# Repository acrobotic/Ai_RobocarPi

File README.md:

# Ai_RobocarPi

Hardware, Software, and Documentation files for a Raspberry Pi-powered autonomous wheeled robot.

## Description

Developed by MakerBro for ACROBOTIC Industries.  Please consider buying 
products from us to help fund future Open-Source projects like this! We'll
always put our best effort in every project, and release all our design 
files and code for you to use. 

Visit our online shop, which is located at:

   * https://acrobotic.com/

## License

Released under the MIT license. Please check LICENSE.txt for more information. 
All text above must be included in any redistribution.

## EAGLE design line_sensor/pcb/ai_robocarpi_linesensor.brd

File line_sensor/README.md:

## line_sensor 

PCB design files (EAGLE) of an analog optical detector for measuring differences
in light levels. Features 3 QRE1113 reflective sensors and 1 LDR.

## Description

Visit our online shop at:

   * https://acrobotic.com/

Designed by ACROBOTIC Industries.  Please consider buying products from us to 
help fund future Open-Source projects like this! We’ll always put our best 
effort in every project, and release all our design files and code for you to 
use. 

## License

Released under the Creative Commons Attribution, Share-Alike license. Please 
check LICENSE.txt for more information. All text above must be included in any 
redistribution.

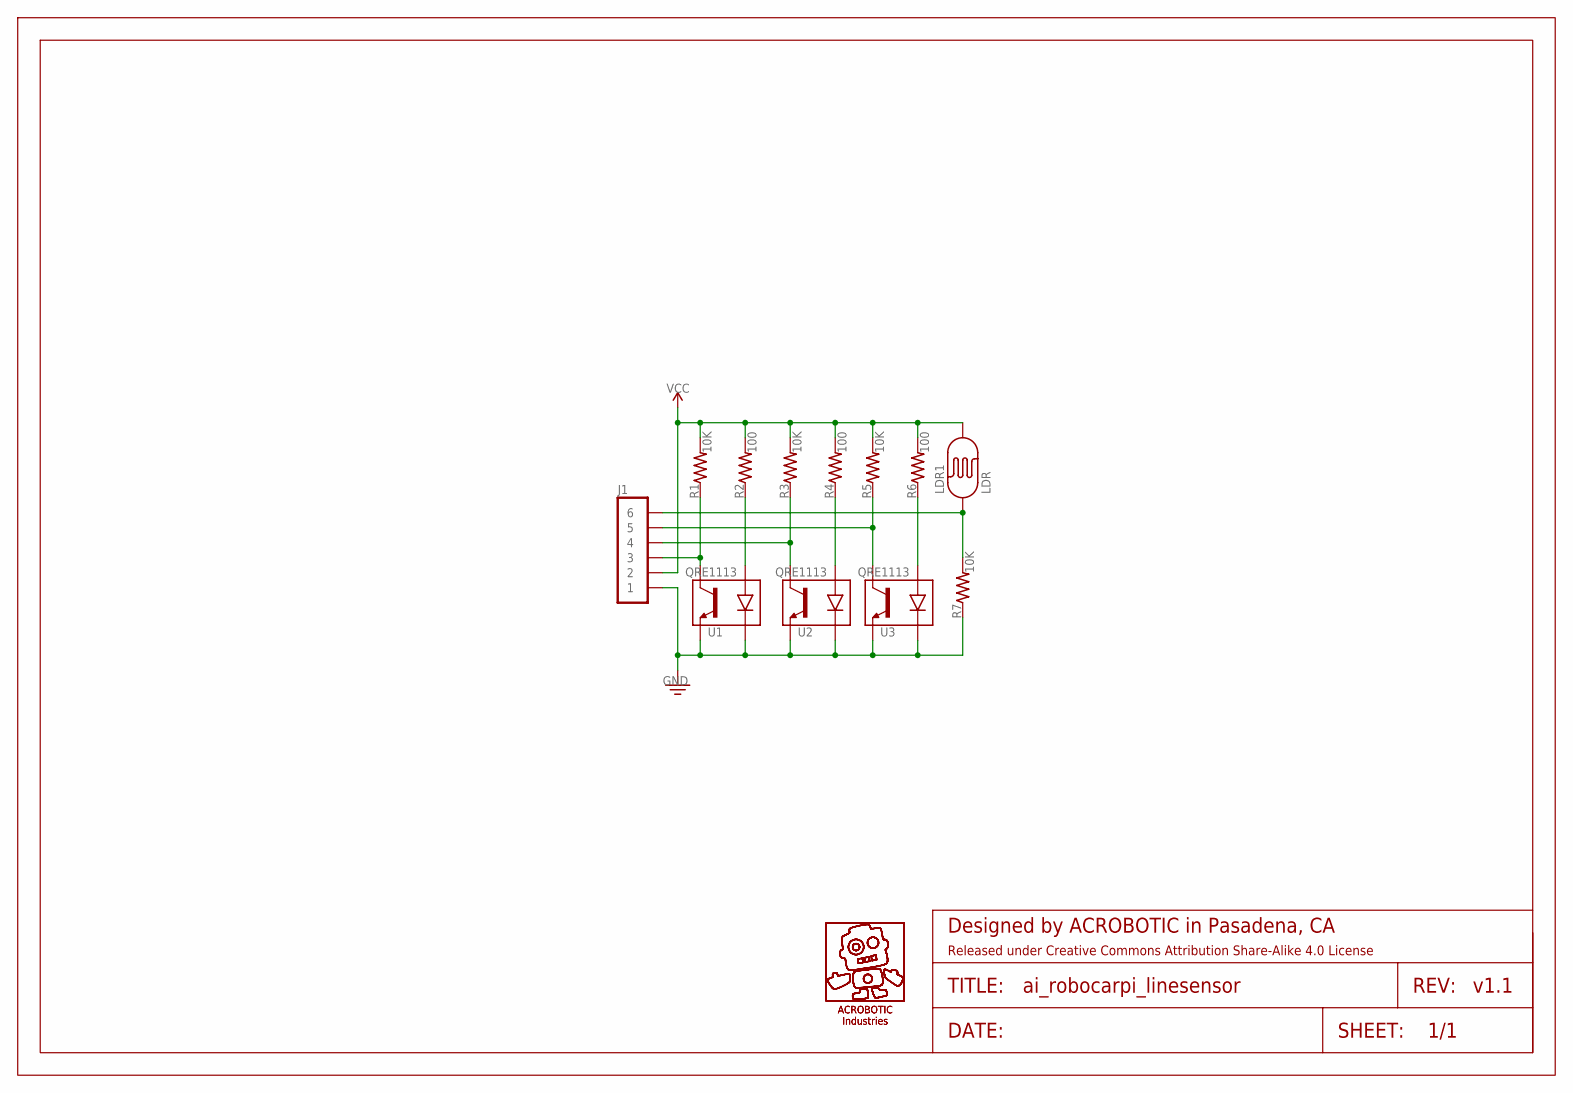
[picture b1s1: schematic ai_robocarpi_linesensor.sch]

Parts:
FRAME1: FRAME-LETTER; CREATIVE-COMMONS
J1: 1X06
LDR1: LDR-PTH; LDR
R1, R3, R5, R7: 10K; RES-0603
R2, R4, R6: 100; RES-0603
U1, U2, U3: QRE1113
U$4, U$5: AI-LOGOXS; AI-LOGO-XS

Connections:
C: J1.4, R3.1, U2.3 (CO)
GND: J1.1, R7.1, U1.2 (CA), U1.4 (E), U2.2 (CA), U2.4 (E), U3.2 (CA), U3.4 (E)
L: J1.3, R1.1, U1.3 (CO)
LDR: J1.6, LDR1.1, R7.2
unnamed: R2.1, U1.1 (A)
unnamed: R4.1, U2.1 (A)
unnamed: R6.1, U3.1 (A)
R: J1.5, R5.1, U3.3 (CO)
VCC: J1.2, LDR1.2, R1.2, R2.2, R3.2, R4.2, R5.2, R6.2

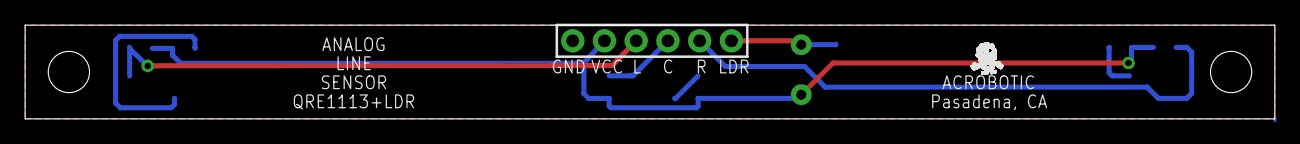
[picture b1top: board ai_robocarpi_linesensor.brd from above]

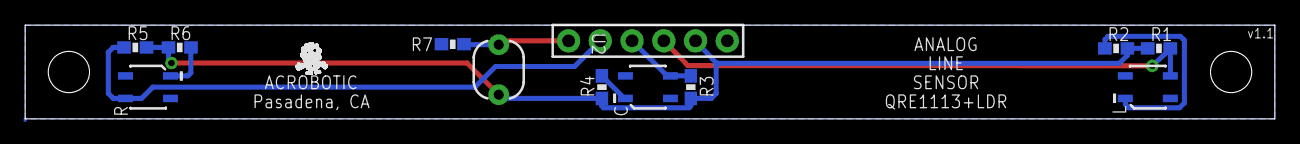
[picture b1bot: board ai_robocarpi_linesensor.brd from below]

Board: 2 copper layers, 100.0 x 7.5 mm, 17 parts (12 on the bottom side), 9 nets.

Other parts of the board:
U$2, U$3: STAND-OFF-4

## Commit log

2018-02-28 adding line sensor files
2018-02-28 adding chassis files

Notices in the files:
parts and their libraries:
Ai_Miscellany: Attribution Share-Alike 4.0 License
Ai_Miscellany: https://creativecommons.org/licenses/by-sa/4.0
Ai_Miscellany: Released under Creative Commons Attribution Share-Alike 4.0 License
